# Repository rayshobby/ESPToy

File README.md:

ESPToy
======

ESPToy is an open-source development board for the ESP8266 WiFi module

- v1 has an on-board avr (atmega644) microcontroller which communicates with an external ESP8266-01 module through serial.

- v1.2x has built-in ESP12 WiFi chip, color LED, button, LiPo battery jack and charging chip, microUSB connector and CH340G USB-serial. Its demo program is in arduino/v1.2x folder. Uploading new program requires bootloading procedure (i.e. hold the on-board button while plugging in USB to enter bootloading mode).

- v2.0 has added auto reset circuit (eliminating bootloading procedure), changed LED to WS2812 (Neopixel) type, added a mini buzzer, light sensor and solder jumper to enable/disable the sensor. Its demo program is in arduino/v2.0 folder. V2.0 is fully compatible with LOLIN Wemos D1 Mini.

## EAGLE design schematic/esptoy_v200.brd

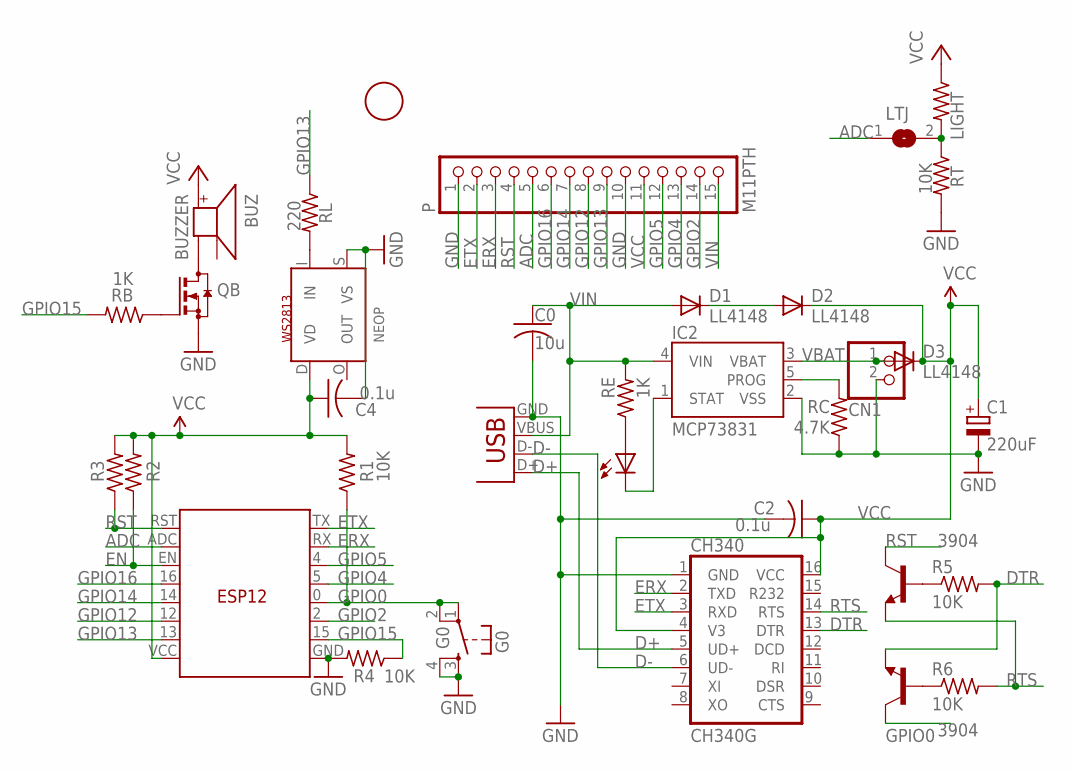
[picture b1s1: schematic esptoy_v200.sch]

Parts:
1F: FIDUCIAL; FIDUCIAL_1MM
BUZ: BUZZER; SMT-8585-BUZZER
C0: 10u; C0805K
C1: 220uF; CT3528
C2, C4: 0.1u; C0603K
CH340: CH340G; SO16
CHG: 0805; CHIPLED_0805
CN1: JST_2PIN-SMT-RA; JST-PH-2-SMT-RA
D1, D2, D3: LL4148; DO-214AC
G0: G0; TACTILE_SWITCH_SMD
IC2: MCP73831; SOT23-5
LIGHT: 100K; R1206
LTJ: SJ
NEOP: WS2813; RGBLED5050_4
P: M11PTH; 1X15-CB
QB: AO3400; SOT23
R1, R2, R3, R4, R5, R6: 10K; R0603
RB: 1K; R0603
RC: 4.7K; R0603
RE: 1K; R0603
RL: 220; R0603
RT: 10K; R0603
T1, T2: 3904; SOT23-BEC
U$1: ESP8266; ESP12
X3: USBMICROB2; USB-MICROB2

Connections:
ADC: LTJ.1, P.5, U$1.ADC
ADC1: LIGHT.2, LTJ.2, RT.1
D+: CH340.5 (UD+), X3.D+
D-: CH340.6 (UD-), X3.D-
DTR: CH340.13 (DTR), R5.2, T2.E
EN: R2.1, U$1.EN
ERX: CH340.2 (TXD), P.3, U$1.RX
ETX: CH340.3 (RXD), P.2, U$1.TX
GND: C0.2, C1.-, C2.2, C4.2, CH340.1 (GND), CN1.2 (1), G0.3, G0.4, IC2.2 (VSS), NEOP.S (VS), P.1, P.10, QB.2 (S), R4.2, RC.1, RT.2, U$1.GND, X3.GND
GPIO0: G0.1, G0.2, R1.1, T2.C, U$1.0 (G0)
GPIO2: P.14, U$1.2 (G2)
GPIO4: P.13, U$1.5 (G5)
GPIO5: P.12, U$1.4 (G4)
GPIO12: P.8, U$1.12 (G12)
GPIO13: P.9, RL.1, U$1.13 (G13)
GPIO14: P.7, U$1.14 (G14)
GPIO15: R4.1, RB.2, U$1.15 (G15)
GPIO16: P.6, U$1.16 (G16)
unnamed: D1.C, D2.A
unnamed: R5.1, T1.B
unnamed: IC2.5 (PROG), RC.2
unnamed: CHG.A, RE.1
unnamed: CHG.C, IC2.1 (STAT)
unnamed: R6.1, T2.B
unnamed: BUZ.-, QB.3 (D)
unnamed: QB.1 (G), RB.1
unnamed: NEOP.I (IN), RL.2
RST: P.4, R3.1, T1.C, U$1.RST
RTS: CH340.14 (RTS), R6.2, T1.E
VBAT: CN1.1 (2), D3.A, IC2.3 (VBAT)
VCC: BUZ.+, C1.+, C2.1, C4.1, CH340.4 (V3), CH340.16 (VCC), D2.C, D3.C, LIGHT.1, NEOP.D (VD), P.11, R1.2, R2.2, R3.2, U$1.VCC
VIN: C0.1, D1.A, IC2.4 (VIN), P.15, RE.2, X3.VBUS

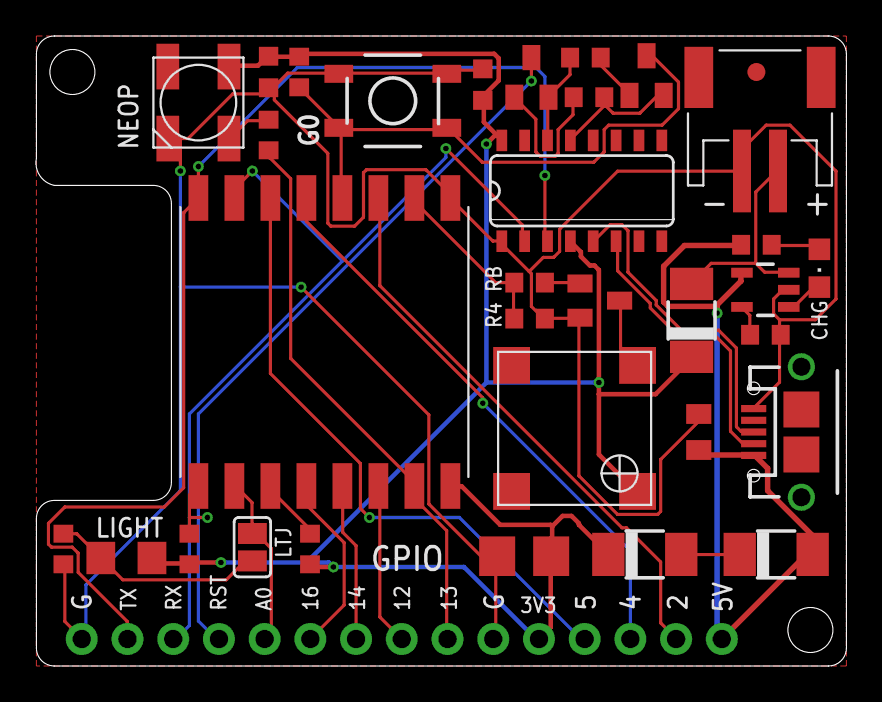
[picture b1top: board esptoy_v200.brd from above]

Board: 2 copper layers, 45.0 x 35.0 mm, 34 parts (0 on the bottom side), 32 nets.

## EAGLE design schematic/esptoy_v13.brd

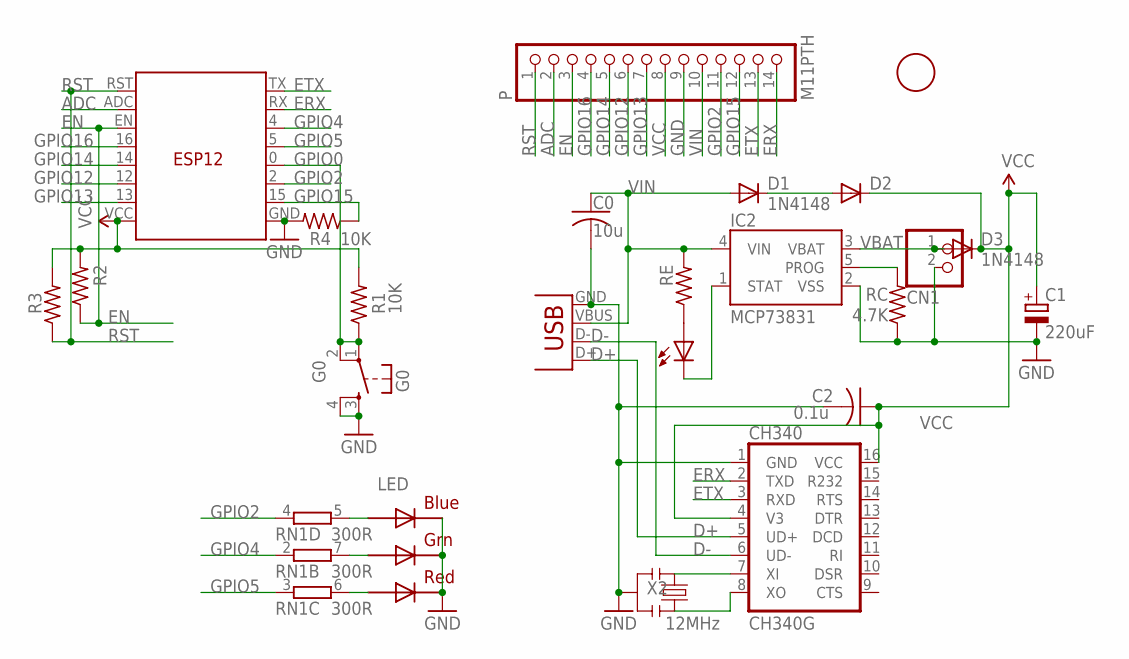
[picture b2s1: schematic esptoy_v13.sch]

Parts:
1F: FIDUCIAL; FIDUCIAL_1MM
C0: 10u; C0805K
C1: 220uF; CT3528
C2: 0.1u; C0603K
CH340: CH340G; SO16
CHG: 0805; CHIPLED_0805
CN1: JST_2PIN-SMT-RA; JST-PH-2-SMT-RA
D1, D3: 1N4148; DO-214AC
D2: DIODE-DO-214AC; DO-214AC
G0: G0; TACTILE_SWITCH_SMD
IC2: MCP73831; SOT23-5
LED: RGBLED5050
P: M11PTH; 1X14-CB
R1, R4: 10K; R0603
R2, R3: R-US_R0603; R0603
RC: 4.7K; R0603
RE: R-US_R0603; R0603
RN1: 300R; EXB38V
U$1: ESP12
X2: 12MHz; RESONATOR-SMD
X3: USBMICROB2; USB-MICROB2

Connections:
ADC: P.2, U$1.ADC
D+: CH340.5 (UD+), X3.D+
D-: CH340.6 (UD-), X3.D-
EN: P.3, R2.1, U$1.EN
ERX: CH340.2 (TXD), P.14, U$1.RX
ETX: CH340.3 (RXD), P.13, U$1.TX
GND: C0.2, C1.-, C2.2, CH340.1 (GND), CN1.2 (1), G0.3, G0.4, IC2.2 (VSS), LED.4 (BLUE_C), LED.5 (RED_C), LED.6 (GREEN_C), P.9, R4.2, RC.1, U$1.GND, X2.2, X3.GND
GPIO0: G0.1, G0.2, R1.1, U$1.0 (G0)
GPIO2: P.11, RN1.4 (1), U$1.2 (G2)
GPIO4: RN1.2 (1), U$1.4 (G4)
GPIO5: RN1.3 (1), U$1.5 (G5)
GPIO12: P.6, U$1.12 (G12)
GPIO13: P.7, U$1.13 (G13)
GPIO14: P.5, U$1.14 (G14)
GPIO15: P.12, R4.1, U$1.15 (G15)
GPIO16: P.4, U$1.16 (G16)
unnamed: D1.C, D2.A
unnamed: LED.3 (BLUE_A), RN1.5 (2)
unnamed: IC2.5 (PROG), RC.2
unnamed: CHG.A, RE.1
unnamed: CHG.C, IC2.1 (STAT)
unnamed: LED.1 (GREEN_A), RN1.7 (2)
unnamed: LED.2 (RED_A), RN1.6 (2)
unnamed: CH340.7 (XI), X2.1
unnamed: CH340.8 (XO), X2.3
RST: P.1, R3.1, U$1.RST
VBAT: CN1.1 (2), D3.A, IC2.3 (VBAT)
VCC: C1.+, C2.1, CH340.4 (V3), CH340.16 (VCC), D2.C, D3.C, P.8, R1.2, R2.2, R3.2, U$1.VCC
VIN: C0.1, D1.A, IC2.4 (VIN), P.10, RE.2, X3.VBUS

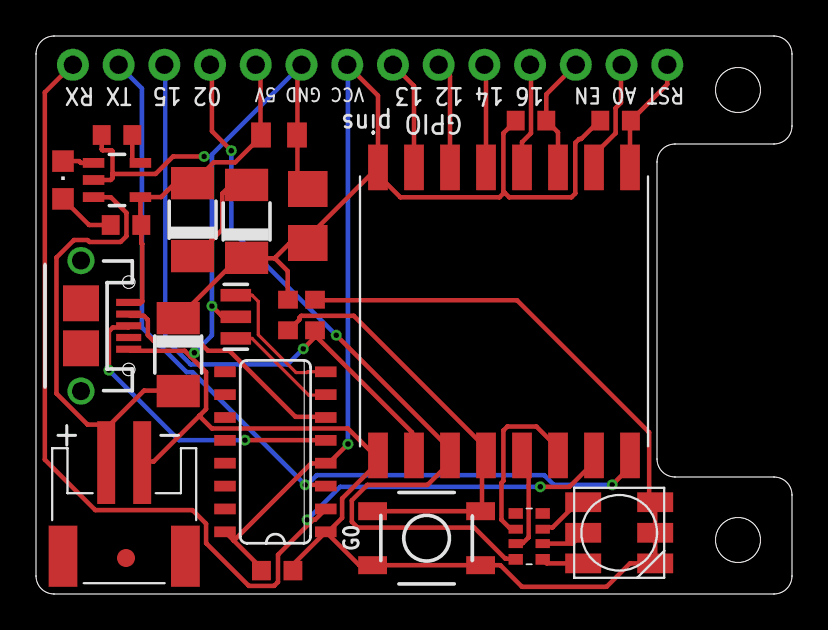
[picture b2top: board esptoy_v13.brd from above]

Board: 2 copper layers, 42.0 x 31.0 mm, 24 parts (0 on the bottom side), 29 nets.

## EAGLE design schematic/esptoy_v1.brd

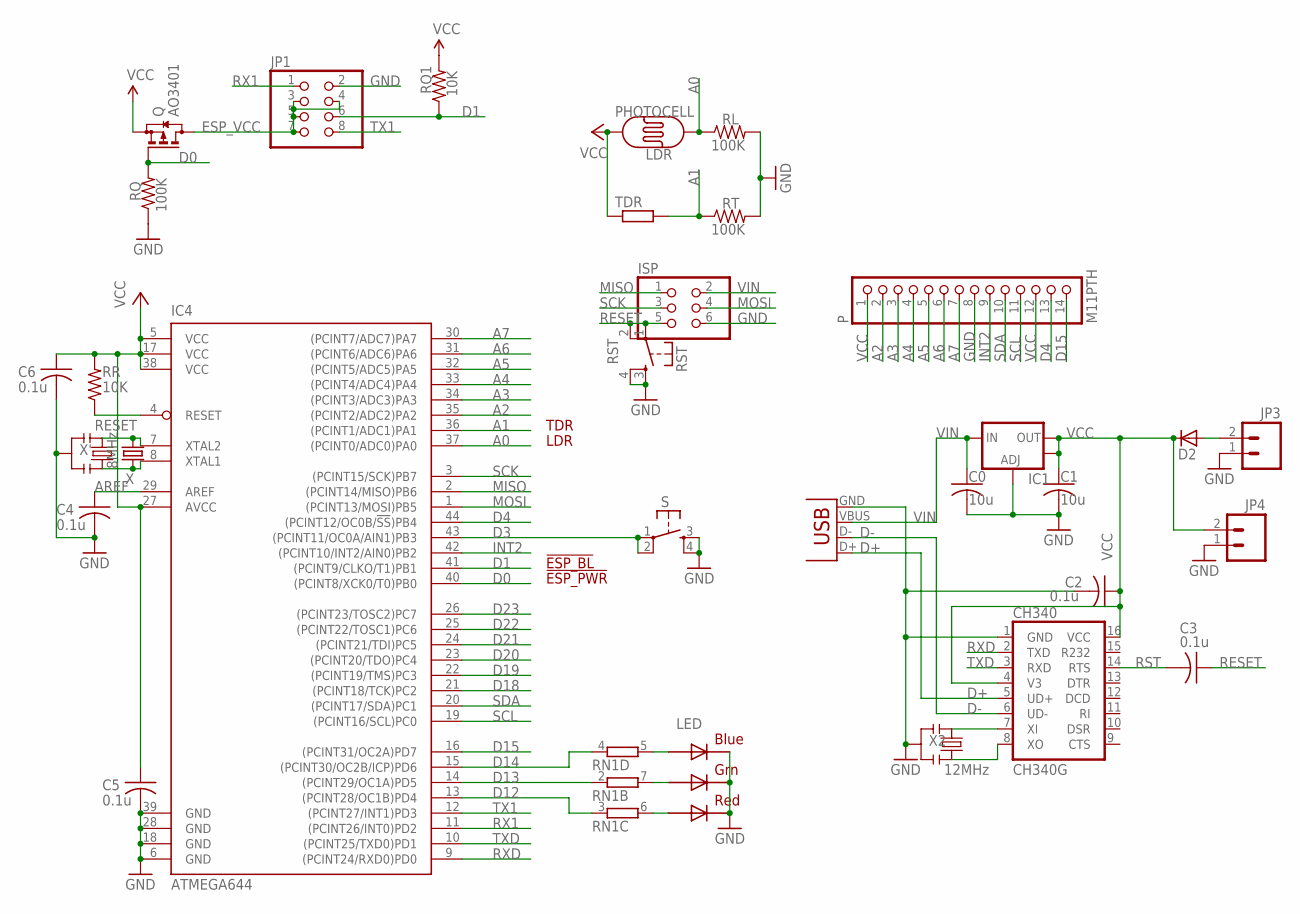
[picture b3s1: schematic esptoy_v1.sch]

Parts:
C0, C1: 10u; C0805K
C2, C3, C4, C6: 0.1u; C0603
C5: 0.1u; C0603K
CH340: CH340G; SO16
D2: DIODESMA; SMA-DIODE
IC1: V_REG_LM1117SOT223; SOT223
IC4: ATMEGA644; TQFP44
ISP: PINHD-2X3; 2X03
JP1: PINHD-2X4; 2X04
JP3: M02-JST-2MM-SMT; S2B-PH
JP4: M02PTH; 1X02
LDR: PHOTOCELL
LED: RGBLED5050
P: M11PTH; 1X14-CB
Q: AO3401; SOT23
RL: 100K; R0805
RN1: 4R-NEXB38V; EXB38V
RQ: 100K; R0805
RQ1: 10K; R0603
RR: 10K; R0603
RST: RST; TACTILE_SWITCH_SMD
RT: 100K; R0805
S: TAC_SWITCHSMD; TACTILE_SWITCH_SMD
TDR: R-EU_V526-0; V526-0
X: 8MHz; TC26V
X1: USBSMD; USB-MINIB
X2: 12MHz; RESONATOR-SMD
X': 12MHz; RESONATOR-SMD

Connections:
A0: IC4.37 ((PCINT0/ADC0)PA0), LDR.1, RL.1
A1: IC4.36 ((PCINT1/ADC1)PA1), RT.1, TDR.2
A2: IC4.35 ((PCINT2/ADC2)PA2), P.2
A3: IC4.34 ((PCINT3/ADC3)PA3), P.3
A4: IC4.33 ((PCINT4/ADC4)PA4), P.4
A5: IC4.32 ((PCINT5/ADC5)PA5), P.5
A6: IC4.31 ((PCINT6/ADC6)PA6), P.6
A7: IC4.30 ((PCINT7/ADC7)PA7), P.7
AREF: C4.1, IC4.29 (AREF)
D0: IC4.40 ((PCINT8/XCK0/T0)PB0), Q.1 (G), RQ.2
D1: IC4.41 ((PCINT9/CLKO/T1)PB1), JP1.6, RQ1.1
D3: IC4.43 ((PCINT11/OC0A/AIN1)PB3), S.1, S.2
D4: IC4.44 ((PCINT12/OC0B/!SS!)PB4), P.13
D12: IC4.13 ((PCINT28/OC1B)PD4), RN1.3 (1)
D13: IC4.14 ((PCINT29/OC1A)PD5), RN1.2 (1)
D14: IC4.15 ((PCINT30/OC2B/ICP)PD6), RN1.4 (1)
D15: IC4.16 ((PCINT31/OC2A)PD7), P.14
D18: IC4.21 ((PCINT18/TCK)PC2)
D19: IC4.22 ((PCINT19/TMS)PC3)
D20: IC4.23 ((PCINT20/TDO)PC4)
D21: IC4.24 ((PCINT21/TDI)PC5)
D22: IC4.25 ((PCINT22/TOSC1)PC6)
D23: IC4.26 ((PCINT23/TOSC2)PC7)
D+: CH340.5 (UD+), X1.D+
D-: CH340.6 (UD-), X1.D-
ESP_VCC: JP1.3, JP1.4, JP1.5, JP1.7, Q.3 (D)
GND: C0.2, C1.2, C2.2, C4.2, C5.2, C6.2, CH340.1 (GND), IC1.1 (ADJ), IC4.6 (GND), IC4.18 (GND), IC4.28 (GND), IC4.39 (GND), ISP.6, JP1.2, JP3.1, JP4.1, LED.4 (BLUE_C), LED.5 (RED_C), LED.6 (GREEN_C), P.8, RL.2, RQ.1, RST.3, RST.4, RT.2, S.3, S.4, X1.GND, X2.2, X'.2
INT2: IC4.42 ((PCINT10/INT2/AIN0)PB2), P.9
MISO: IC4.2 ((PCINT14/MISO)PB6), ISP.1
MOSI: IC4.1 ((PCINT13/MOSI)PB5), ISP.4
unnamed: D2.A, JP3.2
unnamed: LED.3 (BLUE_A), RN1.5 (2)
unnamed: LED.1 (GREEN_A), RN1.7 (2)
unnamed: LED.2 (RED_A), RN1.6 (2)
unnamed: CH340.7 (XI), X2.1
unnamed: CH340.8 (XO), X2.3
unnamed: IC4.7 (XTAL2), X.2, X'.1
unnamed: IC4.8 (XTAL1), X.1, X'.3
RESET: C3.1, IC4.4 (RESET), ISP.5, RR.1, RST.1, RST.2
RST: C3.2, CH340.14 (RTS)
RX1: IC4.11 ((PCINT26/INT0)PD2), JP1.1
RXD: CH340.2 (TXD), IC4.9 ((PCINT24/RXD0)PD0)
SCK: IC4.3 ((PCINT15/SCK)PB7), ISP.3
SCL: IC4.19 ((PCINT16/SCL)PC0), P.11
SDA: IC4.20 ((PCINT17/SDA)PC1), P.10
TX1: IC4.12 ((PCINT27/INT1)PD3), JP1.8
TXD: CH340.3 (RXD), IC4.10 ((PCINT25/TXD0)PD1)
VCC: C1.1, C2.1, C5.1, C6.1, CH340.4 (V3), CH340.16 (VCC), D2.C, IC1.2 (OUT), IC1.4 (OUT), IC4.5 (VCC), IC4.17 (VCC), IC4.27 (AVCC), IC4.38 (VCC), JP4.2, LDR.2, P.1, P.12, Q.2 (S), RQ1.2, RR.2, TDR.1
VIN: C0.1, IC1.3 (IN), ISP.2, X1.VBUS

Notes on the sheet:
TDR
LDR
!ESP_PWR
!ESP_BL

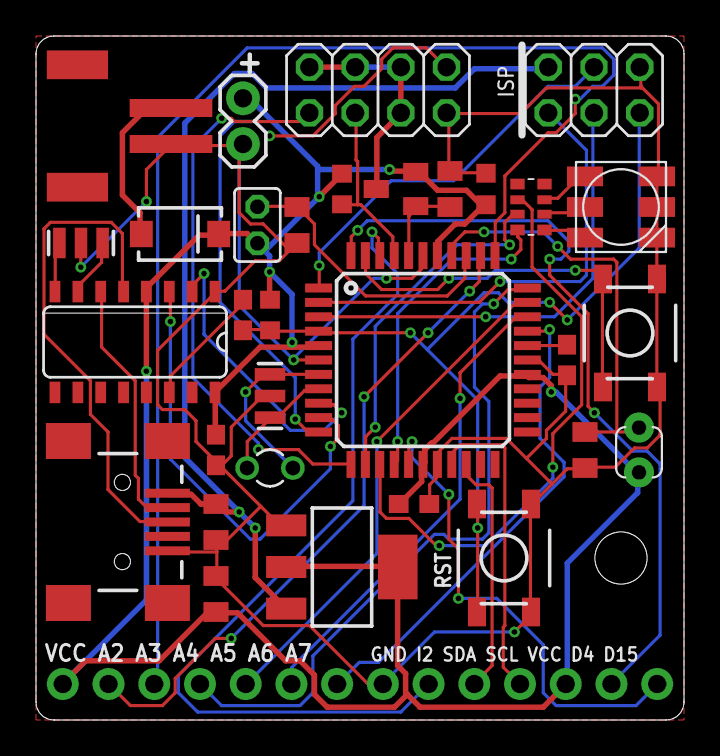
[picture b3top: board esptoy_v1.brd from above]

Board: 2 copper layers, 36.0 x 38.0 mm, 32 parts (0 on the bottom side), 43 nets.

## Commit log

2015-01-03 initial check in of ESPToy Arduino library and hardware design files
2015-01-08 correct board name
2015-01-09 add DefaultDemo
2015-01-09 fix Arduino compiler stack overflow issue (by breaking long strings into shorter ones. seems like an Arduino bug.
2015-01-28 add delay after reset to improve robustness
2015-01-28 reduce buffer size to 500 to improve robustness
2015-01-28 remove caching header
2015-03-30 check in Lua scripts for ESPToy 1.2
2015-04-24 add esptoy 1.21 schematic and Eagle files
2015-05-06 improve startup demo
2015-05-10 update startup demo with a more polished user interface
2015-05-27 add part list, add esptoy 1.22 schematic and board design
2015-05-27 update part list
2016-06-26 move esptoy v1 arduino code to v1 folder, add new v2 folder
2016-06-26 add README.txt in various folders
2016-06-26 add new Default Demo based on Arduino ESP8266 core
2016-06-26 fine tune color gamma
2018-11-05 add v1.24 schematic and board design
2018-11-05 add version 1.3 schematic and board design.
2020-05-05 check in ESPToy v2.0 schematic
2020-05-06 check in ESPToy v2 new version demo program
2020-05-10 change folder names to match hardware version
2020-05-10 modify README to add details

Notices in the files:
parts and their libraries:
SparkFunNew: Licensing: CC v3.0 Share-Alike You are welcome to use this library for commercial purposes.
